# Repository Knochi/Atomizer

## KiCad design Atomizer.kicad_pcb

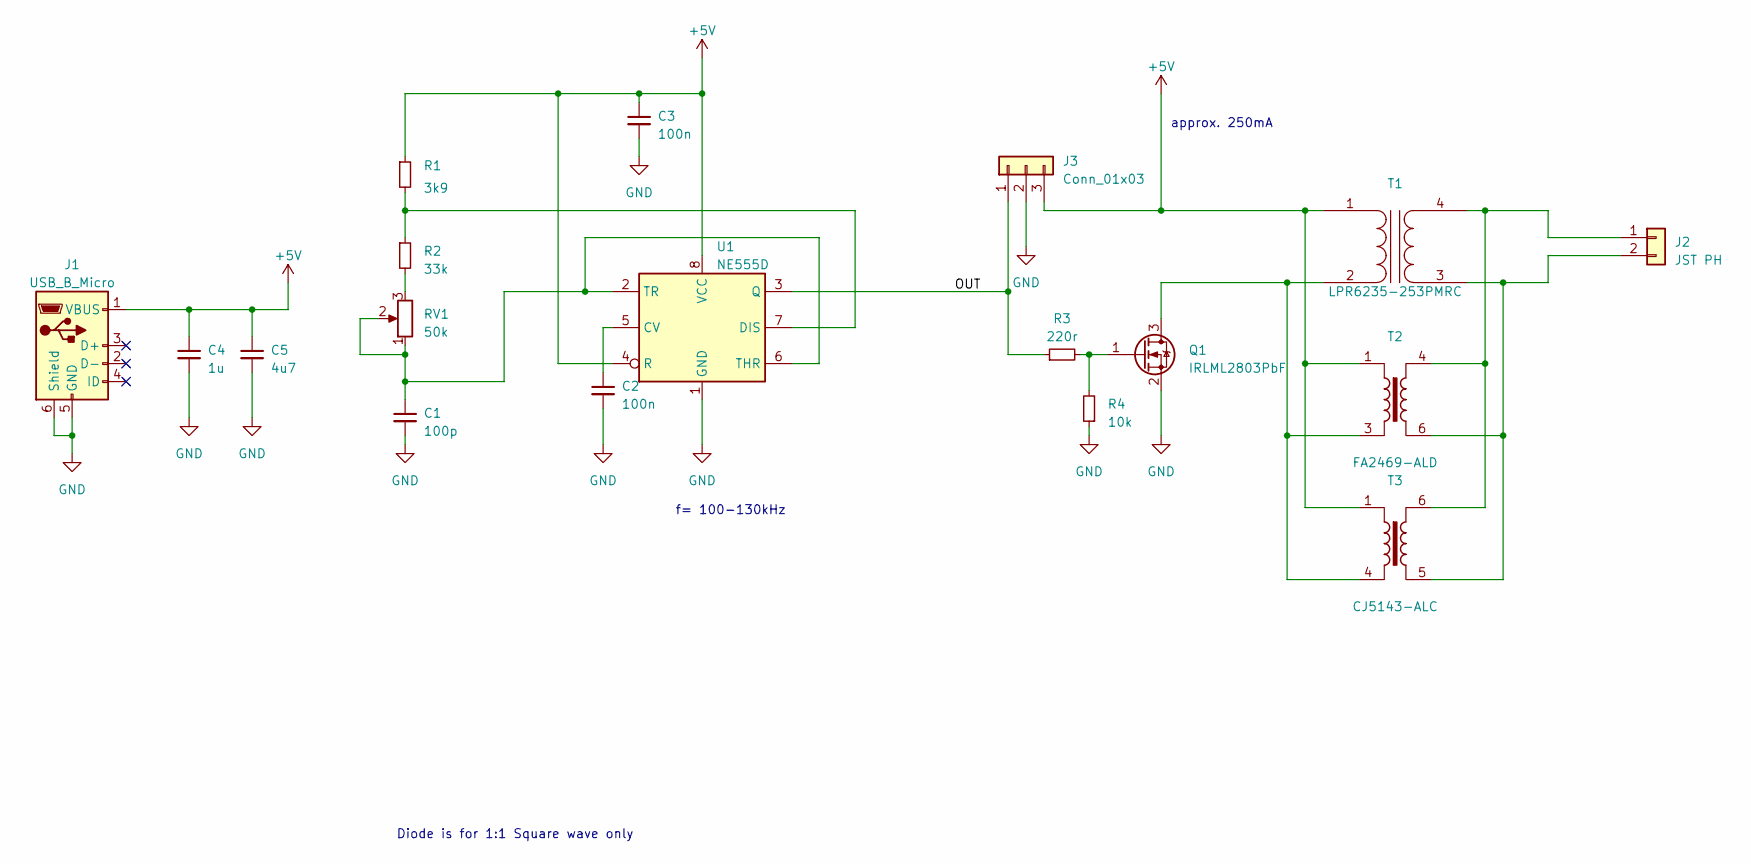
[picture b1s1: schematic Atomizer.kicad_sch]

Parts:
C1: 100p; C_0805_2012Metric
C2, C3: 100n; C_0805_2012Metric
C4: 1u; C_0805_2012Metric
C5: 4u7; C_0805_2012Metric
J1: USB_B_Micro; USB_Micro-B_AMTEK_MIUSB-F5M-BBX-U_Horizontal
J2: JST PH; JST_PH_B2B-PH-K_1x02_P2.00mm_Vertical
J3: Conn_01x03; PinHeader_1x03_P2.54mm_Vertical
Q1: IRLML2803PbF; SOT-23-3
R1: 3k9; R_0805_2012Metric
R2: 33k; R_0805_2012Metric
R3: 220r; R_0805_2012Metric
R4: 10k; R_0805_2012Metric
RV1: 50k; Potentiometer_Bourns_3296W_Vertical; MPN PV36W503C01B00
T1: LPR6235-253PMRC; Transformer_CoilCraft_LPR6235
T2: FA2469-ALD; Transformer_CoilCraft_FA2469
T3: CJ5143-ALC; Transformer_CoilCraft_NCP5080
U1: NE555D; SOIC-8_3.9x4.9mm_P1.27mm

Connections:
+5V: C3.1, C4.1, C5.1, J1.1 (VBUS), J3.3, R1.1, T1.1 (AA), T2.1, T3.1, U1.4 (R), U1.8 (VCC)
/OUT: J3.1, R3.1, U1.3 (Q)
GND: C1.2, C2.2, C3.2, C4.2, C5.2, J1.5 (GND), J1.6 (Shield), J3.2, Q1.2 (S), R4.1, U1.1 (GND)
unnamed: J2.1, T1.4 (SB), T2.4, T3.6
unnamed: J2.2, T1.3 (SA), T2.6, T3.5
unnamed: Q1.3 (D), T1.2 (AB), T2.3, T3.4
unnamed: Q1.1 (G), R3.2, R4.2
unnamed: R2.2, RV1.3
unnamed: C2.1, U1.5 (CV)
unnamed: R1.2, R2.1, U1.7 (DIS)
unnamed: C1.1, RV1.1, RV1.2, U1.2 (TR), U1.6 (THR)

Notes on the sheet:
approx. 250mA
Diode is for 1:1 Square wave only
f= 100-130kHz

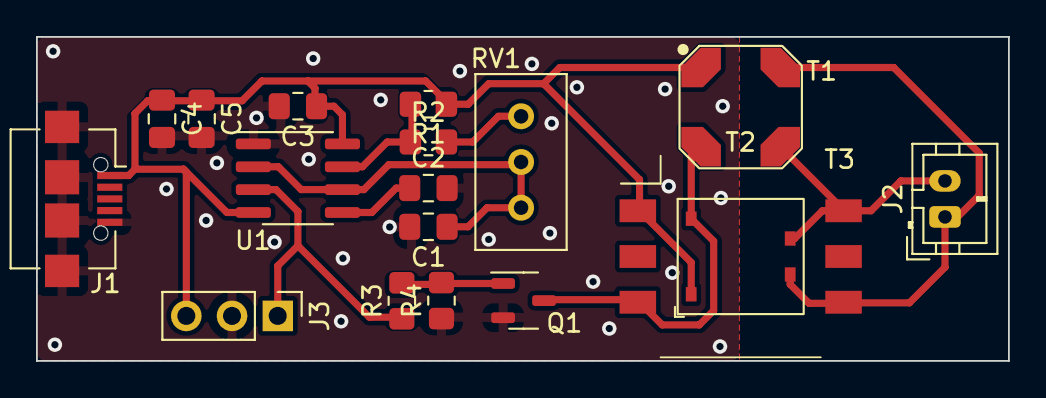
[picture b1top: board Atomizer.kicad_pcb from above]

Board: 2 copper layers, 54.0 x 18.0 mm, 18 parts (0 on the bottom side), 11 nets.

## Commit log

2024-01-17 add gitignoe
2024-01-17 add backups
